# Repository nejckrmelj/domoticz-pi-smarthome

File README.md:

# Smart Home with Domoticz and Raspberry Pi

## Introduction

This repository is a software and hardware source for a smart home project I was working on during one month of practical training at Erasmus+, at Gut Wehlitz in Schkeuditz, Leipzig, Germany. My mentor Aran Talboys gave me a project to control the relay board with Raspberry Pi and Domoticz. The final version works through MQTT. Raspberry uses docker compose to run three services: Mosquitto MQTT broker, Domoticz smart home system and a python hardware client. Hardware client listens on Domoticz's topic and controls the GPIOs which are connected to relays on the relay board. In the current version GPIOs are not fully synced with Domoticz - if GPIO is changed by some other program, change is not reflected by the hardware client.

## Technologies Used

- **Domoticz** (smart home system)
- **MQTT**
- **Docker**

## Local Setup

Before you start, you need to have a remote GPIO access enabled on your Raspberry Pi (enable it in `sudo raspi-config` settings and with `sudo systemctl enable pigpiod` on your Pi).

To run this repo locally, follow these steps:

1. Clone repository `git clone [repo url]`

2. Move to the software directory `cd software`

3. Copy .env.template file to the .env file and edit variables

4. Build and run app with `docker compose build` and `docker compose up`

5. Go to [http://localhost:8080/](http://localhost:8080/) or [https://localhost:443/](https://localhost:443/)

6. On Domoticz add hardware with type _MQTT Client Gateway with LAN interface_, remote address _mosquitto_ and username and password from you .env file

7. Add new hardware for every useful GPIO on the Raspberry Pi with name _GPIO [pin number]_ and type _Dummy (Does nothing, use for virtual switches only_

8. Add switches with hardware _GPIO [pin number]_ with any type and name

### Clone Repo With Git Sparse Checkout

To clone only specific folder (e.g. on the Rapsberry Pi you only need a software folder) use git sparse: checkout

1. Init repository localy with `git init` and `git remote add origin [repo url]`

2. Init git sparse checkout `git sparse-checkout init --cone`

3. Specify folder to pull `git sparse-checkout set [folder name]`

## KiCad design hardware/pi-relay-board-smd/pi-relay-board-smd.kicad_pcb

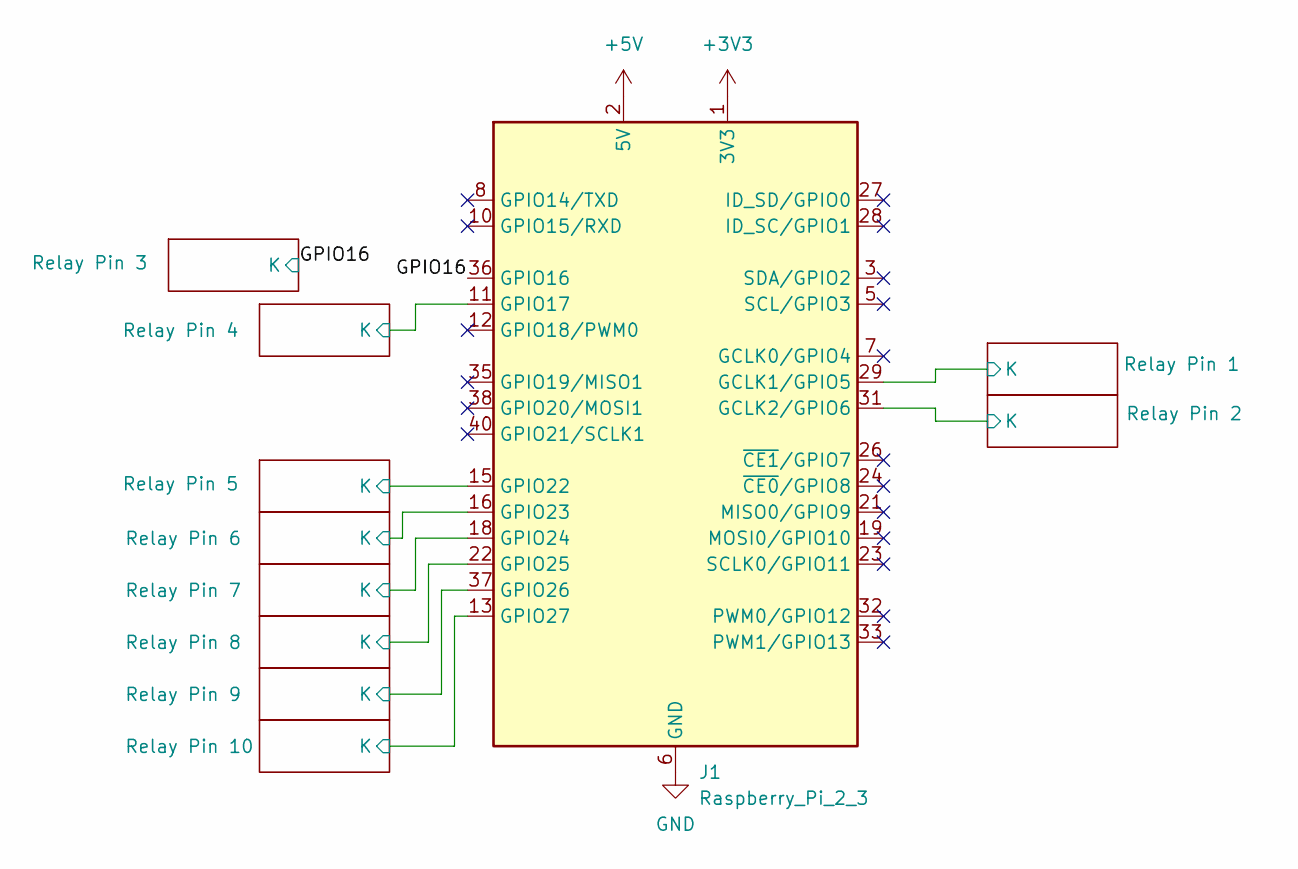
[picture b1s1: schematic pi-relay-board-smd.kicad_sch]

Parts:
J1: Raspberry_Pi_2_3; PinHeader_2x20_P2.54mm_Vertical_SMD

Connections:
+3V3: J1.1 (3V3), J1.17 (3V3)
+5V: J1.2 (5V), J1.4 (5V); also elsewhere on the board
/GPIO16: J1.36 (GPIO16); also elsewhere on the board
/Relay Pin 1/K: J1.29 (GCLK1/GPIO5); also elsewhere on the board
/Relay Pin 2/K: J1.31 (GCLK2/GPIO6); also elsewhere on the board
/Relay Pin 4/K: J1.11 (GPIO17); also elsewhere on the board
/Relay Pin 5/K: J1.15 (GPIO22); also elsewhere on the board
/Relay Pin 6/K: J1.16 (GPIO23); also elsewhere on the board
/Relay Pin 7/K: J1.18 (GPIO24); also elsewhere on the board
/Relay Pin 8/K: J1.22 (GPIO25); also elsewhere on the board
/Relay Pin 9/K: J1.37 (GPIO26); also elsewhere on the board
/Relay Pin 10/K: J1.13 (GPIO27); also elsewhere on the board
GND: J1.6 (GND), J1.9 (GND), J1.14 (GND), J1.20 (GND), J1.25 (GND), J1.30 (GND), J1.34 (GND), J1.39 (GND); also elsewhere on the board

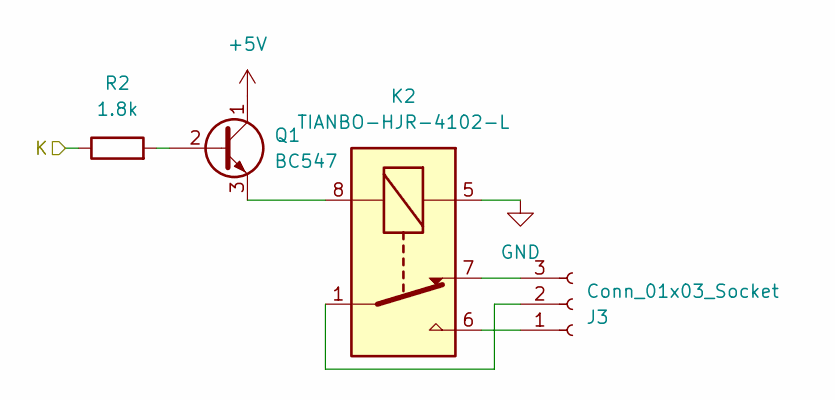
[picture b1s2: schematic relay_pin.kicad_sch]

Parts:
J3: Conn_01x03_Socket; TerminalBlock_Phoenix_PT-1,5-3-3.5-H_1x03_P3.50mm_Horizontal
K2: TIANBO-HJR-4102-L; Relay_SPDT_HJR-4102
Q1: BC547; SOT-23
R2: 1.8k; R_0805_2012Metric_Pad1.20x1.40mm_HandSolder

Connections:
+5V: Q1.1 (C); also elsewhere on the board
/Relay Pin 2/K: R2.1; also elsewhere on the board
GND: K2.5; also elsewhere on the board
unnamed: J3.1, K2.6
unnamed: J3.2, K2.1
unnamed: J3.3, K2.7
unnamed: Q1.2 (B), R2.2
unnamed: K2.8, Q1.3 (E)

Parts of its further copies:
J2, J4, J5, J6, J7, J8, J9, J10, J11: Conn_01x03_Socket; TerminalBlock_Phoenix_PT-1,5-3-3.5-H_1x03_P3.50mm_Horizontal
K1, K3, K4, K5, K6, K7, K8, K9, K10: TIANBO-HJR-4102-L; Relay_SPDT_HJR-4102
Q2, Q3, Q4, Q5, Q6, Q7, Q8, Q9, Q10: BC547; SOT-23
R1, R3, R4, R5, R6, R7, R8, R9, R10: 1.8k; R_0805_2012Metric_Pad1.20x1.40mm_HandSolder

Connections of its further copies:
+5V: Q2.1 (C), Q3.1 (C), Q4.1 (C), Q5.1 (C), Q6.1 (C), Q7.1 (C), Q8.1 (C), Q9.1 (C), Q10.1 (C); also elsewhere on the board
/GPIO16: R3.1; also elsewhere on the board
/Relay Pin 1/K: R1.1; also elsewhere on the board
/Relay Pin 4/K: R4.1; also elsewhere on the board
/Relay Pin 5/K: R5.1; also elsewhere on the board
/Relay Pin 6/K: R6.1; also elsewhere on the board
/Relay Pin 7/K: R7.1; also elsewhere on the board
/Relay Pin 8/K: R8.1; also elsewhere on the board
/Relay Pin 9/K: R9.1; also elsewhere on the board
/Relay Pin 10/K: R10.1; also elsewhere on the board
GND: K1.5, K3.5, K4.5, K5.5, K6.5, K7.5, K8.5, K9.5, K10.5; also elsewhere on the board
unnamed: J2.1, K1.6
unnamed: J2.2, K1.1
unnamed: J2.3, K1.7
unnamed: J4.1, K3.6
unnamed: J4.2, K3.1
unnamed: J4.3, K3.7
unnamed: J5.1, K4.6
unnamed: J5.2, K4.1
unnamed: J5.3, K4.7
unnamed: J6.1, K5.6
unnamed: J6.2, K5.1
unnamed: J6.3, K5.7
unnamed: J7.1, K6.6
unnamed: J7.2, K6.1
unnamed: J7.3, K6.7
unnamed: J8.1, K7.6
unnamed: J8.2, K7.1
unnamed: J8.3, K7.7
unnamed: J9.1, K8.6
unnamed: J9.2, K8.1
unnamed: J9.3, K8.7
unnamed: J10.1, K9.6
unnamed: J10.2, K9.1
unnamed: J10.3, K9.7
unnamed: J11.1, K10.6
unnamed: J11.2, K10.1
unnamed: J11.3, K10.7
unnamed: Q2.2 (B), R1.2
unnamed: K1.8, Q2.3 (E)
unnamed: Q3.2 (B), R3.2
unnamed: K3.8, Q3.3 (E)
unnamed: Q4.2 (B), R4.2
unnamed: K4.8, Q4.3 (E)
unnamed: Q5.2 (B), R5.2
unnamed: K5.8, Q5.3 (E)
unnamed: Q6.2 (B), R6.2
unnamed: K6.8, Q6.3 (E)
unnamed: Q7.2 (B), R7.2
unnamed: K7.8, Q7.3 (E)
unnamed: Q8.2 (B), R8.2
unnamed: K8.8, Q8.3 (E)
unnamed: Q9.2 (B), R9.2
unnamed: K9.8, Q9.3 (E)
unnamed: Q10.2 (B), R10.2
unnamed: K10.8, Q10.3 (E)

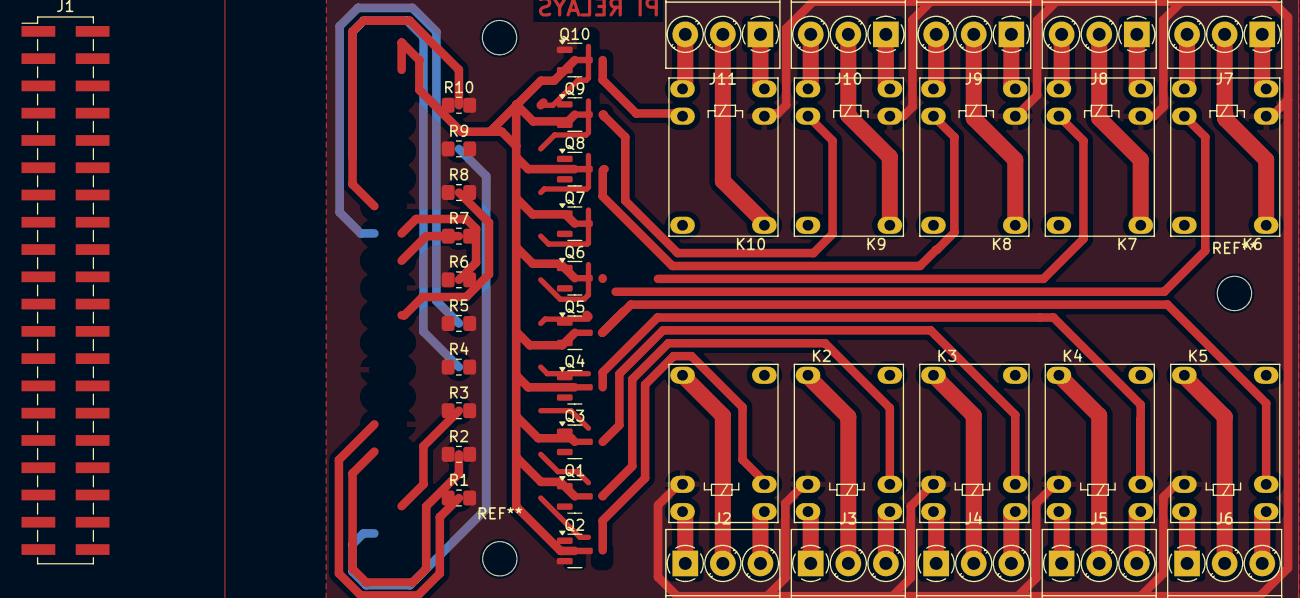
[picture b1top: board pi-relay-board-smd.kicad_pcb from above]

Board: 2 copper layers, 41 parts (0 on the bottom side), 63 nets.

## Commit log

2024-05-29 feat: switched to gpiozero
2024-05-30 feat: get hardware with domoticz api
2024-05-30 feat: initial gpio states
2024-05-30 feat: auto update hardware
2024-06-03 feat: project structure, added pcb
2024-06-04 hardware: change to tht
2024-06-05 feat: pcb bc547 footprint, laser image
2024-06-05 fix: env
2024-06-05 feat: python docker
2024-06-06 fix: laser image scaling
2024-06-06 feat: docker compose mosquitto
2024-06-06 feat: docker compose domoticz
2024-06-06 feat: move python mqtt client to hardware-client
2024-06-06 fix: move .venv
2024-06-09 feat: CNC drill files
2024-06-09 feat: access gpio from docker (remotely)
2024-06-09 fix: gitignore domocookie.txt
2024-06-09 fix: remove port 8888 exposion
2024-06-09 fix: access local pigpio
2024-06-09 fix: delete domocookie.txt
    .gitignore
2024-06-09 fix: mistype
2024-06-10 feat: max restart retries
2024-06-15 fix: compose hardware-client
2024-06-15 fix: final finishes
2024-06-15 fix: delete software/mosquitto/passwd
2024-06-15 fix: mosquitto passwd file
2024-06-15 fix: specify author
2024-06-19 feat: auto create mosquitto user
2024-06-20 feat: add README
2024-06-21 feat: update hardware with https request
2024-06-21 fix: README setup
2024-06-21 fix: mosquitto entrypoint script crlf endings
2024-06-21 fix: env template
2024-06-21 feat: add git sparse checkout to README
2024-06-21 fix: update README
